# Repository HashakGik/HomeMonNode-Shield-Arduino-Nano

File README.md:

HomeMon Node Shield for Arduino Nano
====================================

This Eagle layout can be used to etch a single HomeMon node, in the form of a shield for the Arduino Nano prototyping platform.

The Arduino Nano sketch for this shield is available [here](https://github.com/HashakGik/HomeMonNode-Shield-Arduino-Nano).

<br />

<br />

Features
--------

- Eleven pins can be used as general I/O (e.g. for reading data from sensors)
- Two actuators can be driven by relays
- A power supply bus (5V, 3.3V and ground lines) with fifteen pins is added for convenience
- An [NRF24L01+ 2.4 GHz transceiver](https://www.nordicsemi.com/Products/Low-power-short-range-wireless/nRF24-series) is used for inter-node communication, and serial communication (either via the USB converter of the Arduino or, **optionally**, via an [HC-05 based Bluetooth adapter](https://cdn.makezine.com/uploads/2014/03/hc_hc-05-user-instructions-bluetooth.pdf) allows the node to be connected to a desktop sink running the [HomeMon Viewer Application](https://github.com/HashakGik/HomeMon-MFC-Cpp)
- A trimmer can be used to set the analog voltage reference
- Both the 2.4 GHz transceiver and the optional Bluetooth adapter can be turned on/off by switches (the Bluetooth adapter can additionally be put into AT mode for configuration purposes).

Pinout
------

- Serial pins (`D0` and `D1`): Bluetooth adapter
- SPI pins (`D11` to `D13`), `D2`, `D8` and `D9` pins: radio transceiver
- Analog pins (`A0` to `A7`): directly connected to the `SENSORS` connector
- Digital pins `D2` to `D5`: directly connected to the `SENSORS` connector. (Important note: pin `D2` is also connected to the `IRQ` pin of the transceiver)
- Digital pins `D6` and `D7`: connected to the actuator connectors (`ACT1` and `ACT2` respectively) through two relays
- `AREF`: connected to the analog reference trimmer
- `GND`, `3V3` and `5V`: connected to the power supply connectors
- `RST`, `VIN` and `D10`: unconnected.

Bill of materials
-----------------

- 1x 10k linear trimmer
- 1x Arduino Nano
- 2x Diodes with DO-41 package (e.g. 1N4004)
- 1x DIP switch SPST 1 position (RS-Components code: 877-2100)
- 2x Monostable 5V DC G5LE relays (RS-Components code: 808-8465)
- 2x NPN transistors with TO-92 package (e.g. 2N3904)
- 1x NRF24L01+ module (8 pins breakout board)
- 2x Two-ways PCB terminal blocks with 5.08mm pitch (RS-Components code: 425-8720)

Optionally, for Bluetooth support:

- 1x DIP switch SPST 2 positions (RS-Components code: 877-2113)
- 1x HC-05 Bluetooth module (6 pins breakout board)

Remarks
-------

- The shield relies on the Arduino for power supply (i.e. it doesn't have batteries nor a DC connector, energy must be supplied from the USB connector or the `VIN` pin)
- Arduino pin `D10 (SS)` is left unconnected because the SPI library may malfunction if the pin is set to high when the Arduino is acting as SPI master
- The additional components are defined in the freely available [DIYmodules.org component library](https://www.diymodules.org).

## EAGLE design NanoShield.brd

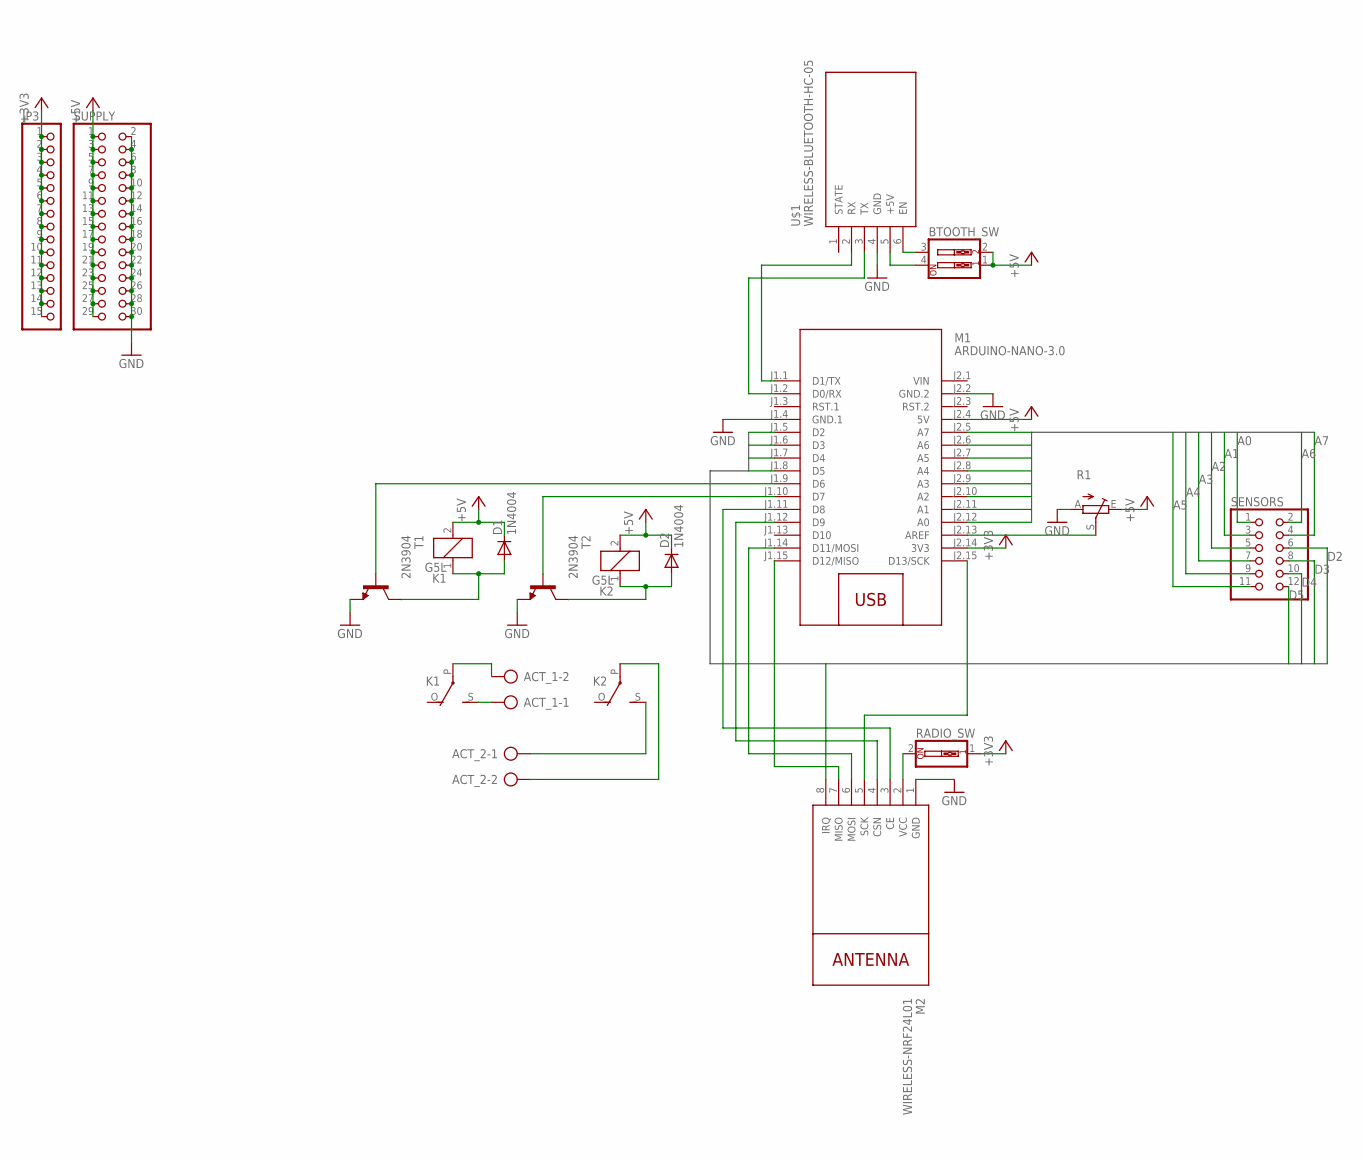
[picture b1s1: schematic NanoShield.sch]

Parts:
ACT_1, ACT_2: AK300/2
BTOOTH_SW: SW_DIP-2; EDG-02
D1, D2: 1N4004; DO41-10
JP3: PINHD-1X15; 1X15
K1, K2: G5L; G5LE
M1: ARDUINO-NANO-3.0
M2: WIRELESS-NRF24L01
R1: TRIM_EU-LI10; LI10
RADIO_SW: SW_DIP-1; EDG-01
SENSORS: PINHD-2X6; 2X06
SUPPLY: PINHD-2X15; 2X15
T1, T2: 2N3904; TO92
U$1: WIRELESS-BLUETOOTH-HC-05

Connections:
+3V3: JP3.1, JP3.2, JP3.3, JP3.4, JP3.5, JP3.6, JP3.7, JP3.8, JP3.9, JP3.10, JP3.11, JP3.12, JP3.13, JP3.14, JP3.15, M1.J2.14 (3V3), RADIO_SW.1
+5V: BTOOTH_SW.1, BTOOTH_SW.2, D1.C, D2.C, K1.2, K2.2, M1.J2.4 (5V), R1.E, SUPPLY.1, SUPPLY.3, SUPPLY.5, SUPPLY.7, SUPPLY.9, SUPPLY.11, SUPPLY.13, SUPPLY.15, SUPPLY.17, SUPPLY.19, SUPPLY.21, SUPPLY.23, SUPPLY.25, SUPPLY.27, SUPPLY.29
A0: M1.J2.12 (A0), SENSORS.1
A1: M1.J2.11 (A1), SENSORS.3
A2: M1.J2.10 (A2), SENSORS.5
A3: M1.J2.9 (A3), SENSORS.7
A4: M1.J2.8 (A4), SENSORS.9
A5: M1.J2.7 (A5), SENSORS.11
A6: M1.J2.6 (A6), SENSORS.2
A7: M1.J2.5 (A7), SENSORS.4
D2: M1.J1.5 (D2), M2.8 (IRQ), SENSORS.6
D3: M1.J1.6 (D3), SENSORS.8
D4: M1.J1.7 (D4), SENSORS.10
D5: M1.J1.8 (D5), SENSORS.12
GND: M1.J1.4 (GND.1), M1.J2.2 (GND.2), M2.1 (GND), R1.A, SUPPLY.2, SUPPLY.4, SUPPLY.6, SUPPLY.8, SUPPLY.10, SUPPLY.12, SUPPLY.14, SUPPLY.16, SUPPLY.18, SUPPLY.20, SUPPLY.22, SUPPLY.24, SUPPLY.26, SUPPLY.28, SUPPLY.30, T1.3 (E), T2.3 (E), U$1.4 (GND)
unnamed: M1.J2.15 (D13/SCK), M2.5 (SCK)
unnamed: M1.J1.14 (D11/MOSI), M2.6 (MOSI)
unnamed: M1.J1.15 (D12/MISO), M2.7 (MISO)
unnamed: M1.J1.1 (D1/TX), U$1.2 (RX)
unnamed: M1.J1.2 (D0/RX), U$1.3 (TX)
unnamed: M2.2 (VCC), RADIO_SW.2
unnamed: M1.J1.12 (D9), M2.4 (CSN)
unnamed: BTOOTH_SW.3, U$1.6 (EN)
unnamed: BTOOTH_SW.4, U$1.5 (+5V)
unnamed: M1.J2.13 (AREF), R1.S
unnamed: M1.J1.11 (D8), M2.3 (CE)
unnamed: M1.J1.10 (D7), T2.2 (B)
unnamed: M1.J1.9 (D6), T1.2 (B)
unnamed: D1.A, K1.1, T1.1 (C)
unnamed: ACT_1.1, K1.S
unnamed: ACT_1.2, K1.P
unnamed: D2.A, K2.1, T2.1 (C)
unnamed: ACT_2.2, K2.P
unnamed: ACT_2.1, K2.S
VIN: M1.J2.1 (VIN)

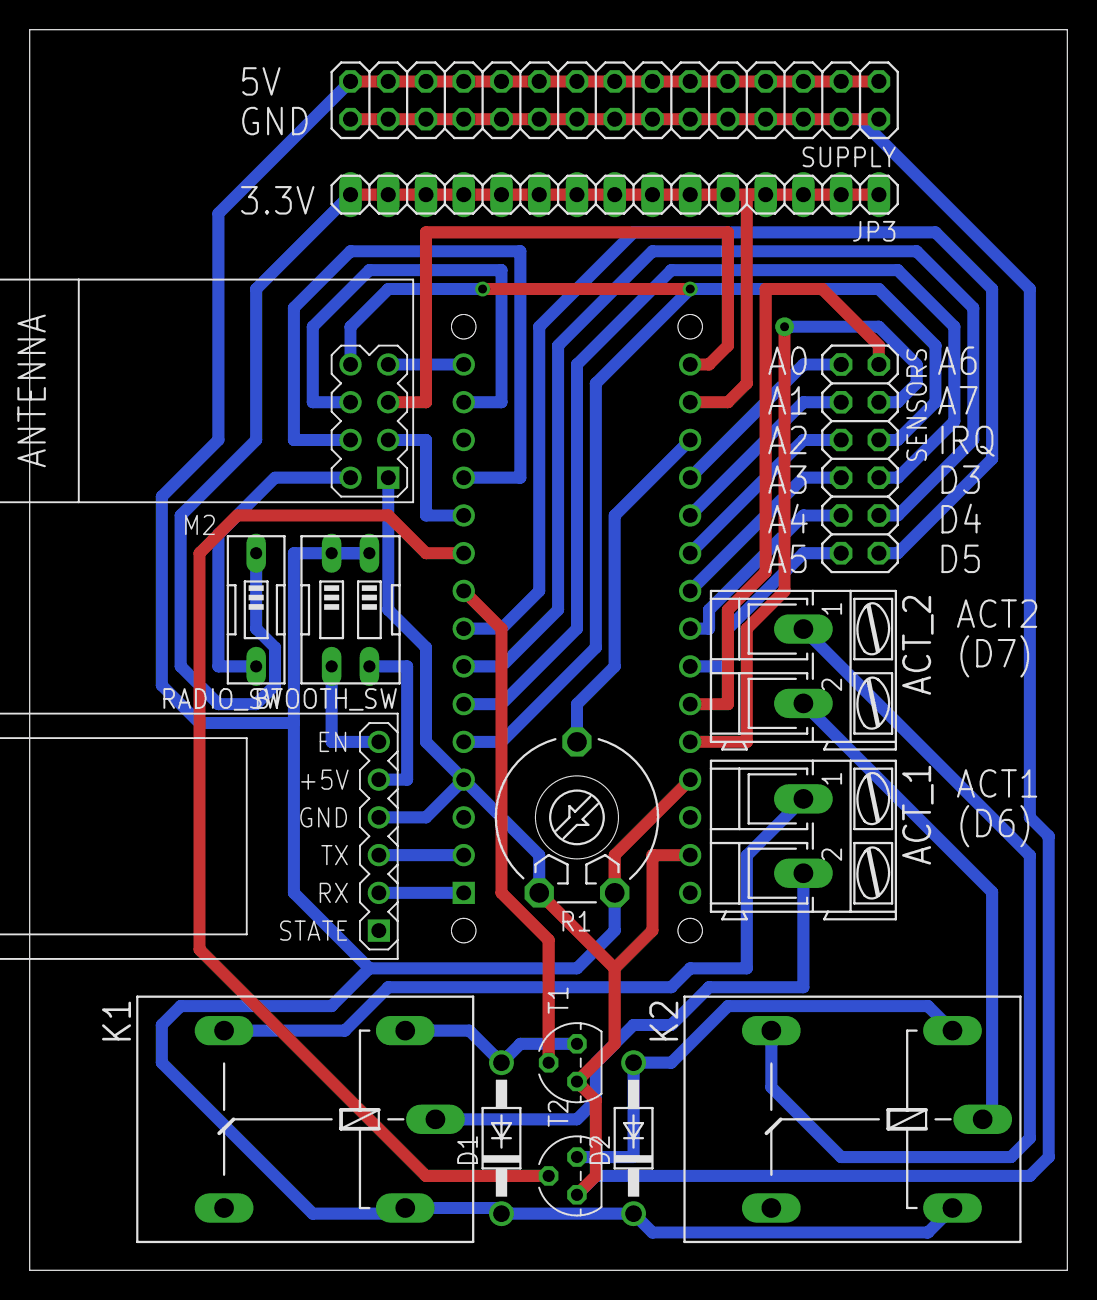
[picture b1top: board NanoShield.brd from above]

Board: 2 copper layers, 69.8 x 83.5 mm, 17 parts (1 on the bottom side), 34 nets.

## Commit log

2019-02-11 Initial commit.
2019-02-20 Fixed missing interrupt pin.
2019-03-01 Fixed README.md
2019-03-09 Fixed bill of materials.

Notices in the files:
parts and their libraries:
diy-modules: Released under the Creative Commons Attribution 4.0 International License: http://creativecommons.org/licenses/by/4.0
